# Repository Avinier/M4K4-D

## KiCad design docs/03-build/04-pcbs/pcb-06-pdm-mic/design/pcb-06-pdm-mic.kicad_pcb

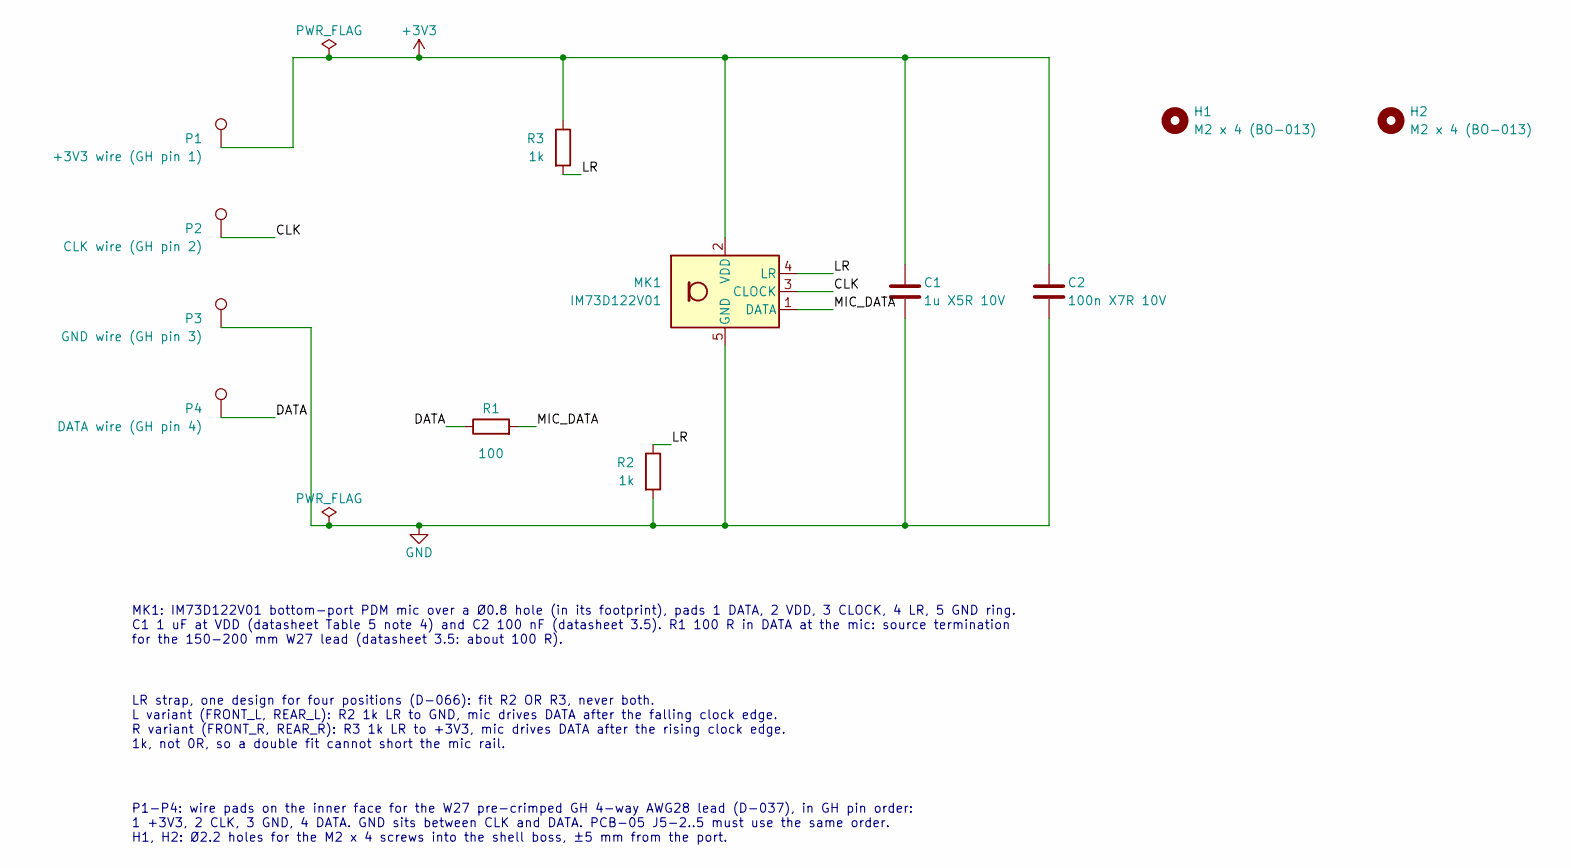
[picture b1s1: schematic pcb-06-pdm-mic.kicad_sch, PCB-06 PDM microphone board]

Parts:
C1: 1u X5R 10V; C_0402_1005Metric
C2: 100n X7R 10V; C_0402_1005Metric
H1, H2: M2 x 4 (BO-013); MountingHole_2.2mm_M2
MK1: IM73D122V01; IM73D122V01_PG-LLGA-5-3; MPN IM73D122V01XTMA1
P1: +3V3 wire (GH pin 1); WirePad_0.9x2.0mm
P2: CLK wire (GH pin 2); WirePad_0.9x2.0mm
P3: GND wire (GH pin 3); WirePad_0.9x2.0mm
P4: DATA wire (GH pin 4); WirePad_0.9x2.0mm
R1: 100; R_0402_1005Metric
R2, R3: 1k; R_0402_1005Metric

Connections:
+3V3: C1.1, C2.1, MK1.2 (VDD), P1.1 (1_1), R3.1
/CLK: MK1.3 (CLOCK), P2.1 (1_1)
/DATA: P4.1 (1_1), R1.1
/LR: MK1.4 (LR), R2.1, R3.2
/MIC_DATA: MK1.1 (DATA), R1.2
GND: C1.2, C2.2, MK1.5 (GND), P3.1 (1_1), R2.2

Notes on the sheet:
MK1: IM73D122V01 bottom-port PDM mic over a Ø0.8 hole (in its footprint), pads 1 DATA, 2 VDD, 3 CLOCK, 4 LR, 5 GND ring. C1 1 uF at VDD (datasheet Table 5 note 4) and C2 100 nF (datasheet 3.5). R1 100 R in DATA at the mic: source termination for the 150-200 mm W27 lead (datasheet 3.5: about 100 R).
LR strap, one design for four positions (D-066): fit R2 OR R3, never both. L variant (FRONT_L, REAR_L): R2 1k LR to GND, mic drives DATA after the falling clock edge. R variant (FRONT_R, REAR_R): R3 1k LR to +3V3, mic drives DATA after the rising clock edge. 1k, not 0R, so a double fit cannot short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
P1-P4: wire pads on the inner face for the W27 pre-crimped GH 4-way AWG28 lead (D-037), in GH pin order: 1 +3V3, 2 CLK, 3 GND, 4 DATA. GND sits between CLK and DATA. PCB-05 J5-2..5 must use the same order. H1, H2: Ø2.2 holes for the M2 x 4 screws into the shell boss, ±5 mm from the port.

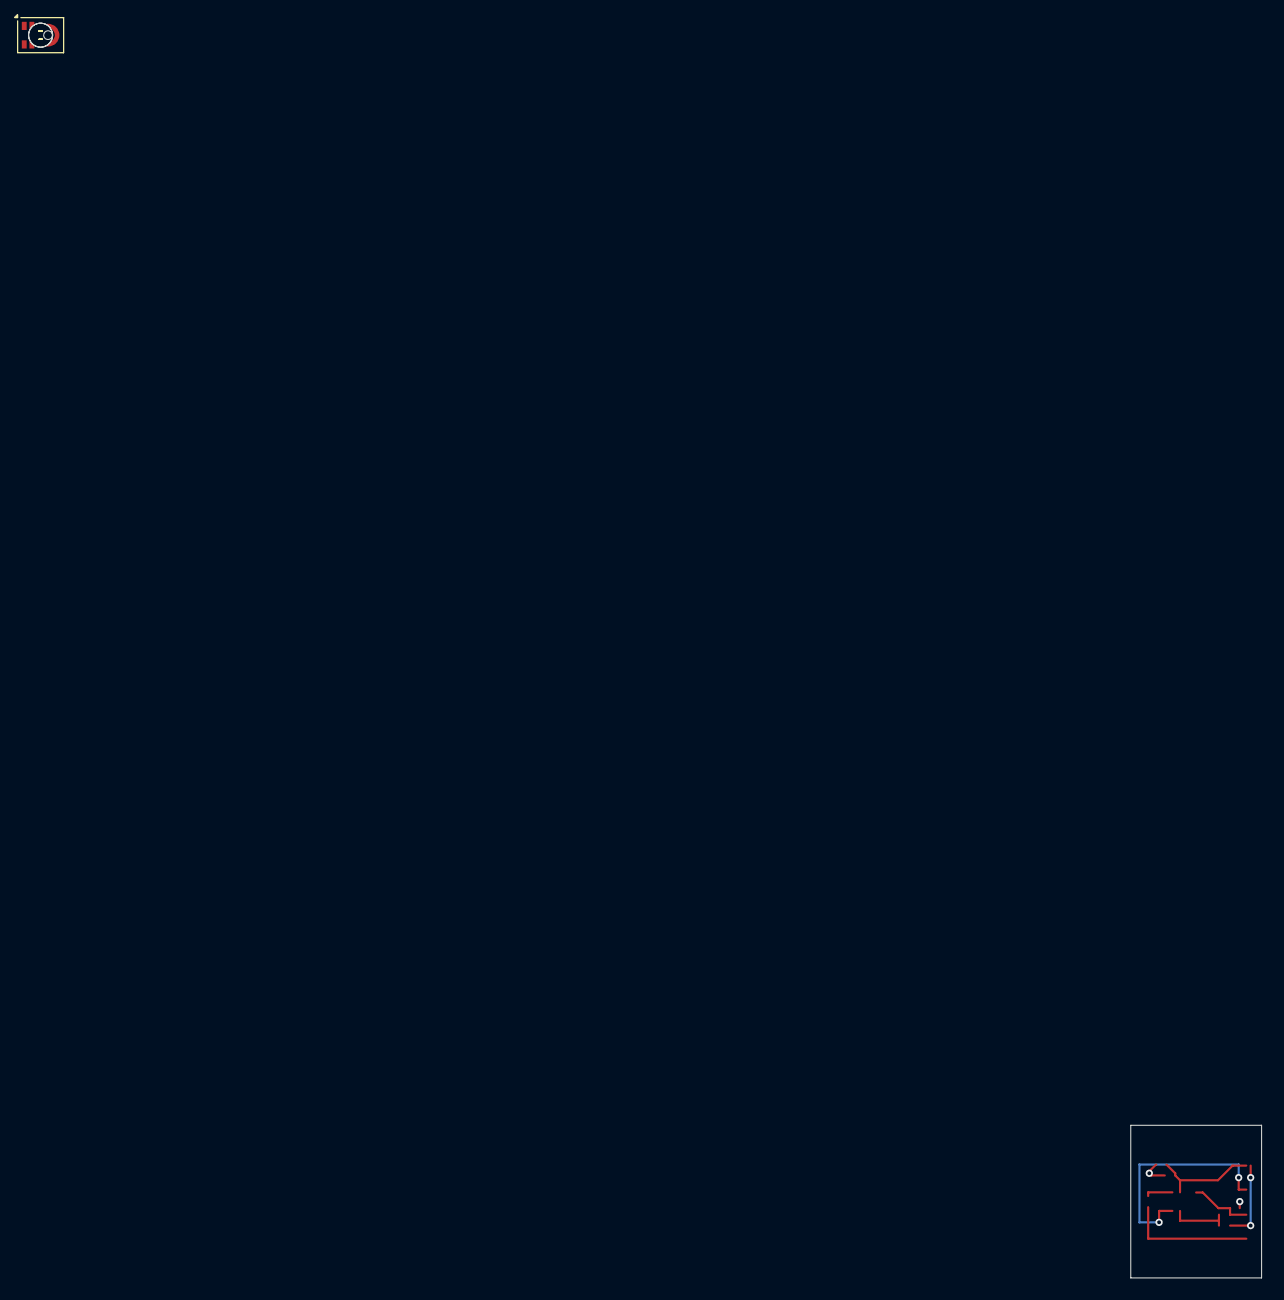
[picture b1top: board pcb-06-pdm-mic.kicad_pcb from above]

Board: 2 copper layers, 12.0 x 14.0 mm, 12 parts (0 on the bottom side), 6 nets.

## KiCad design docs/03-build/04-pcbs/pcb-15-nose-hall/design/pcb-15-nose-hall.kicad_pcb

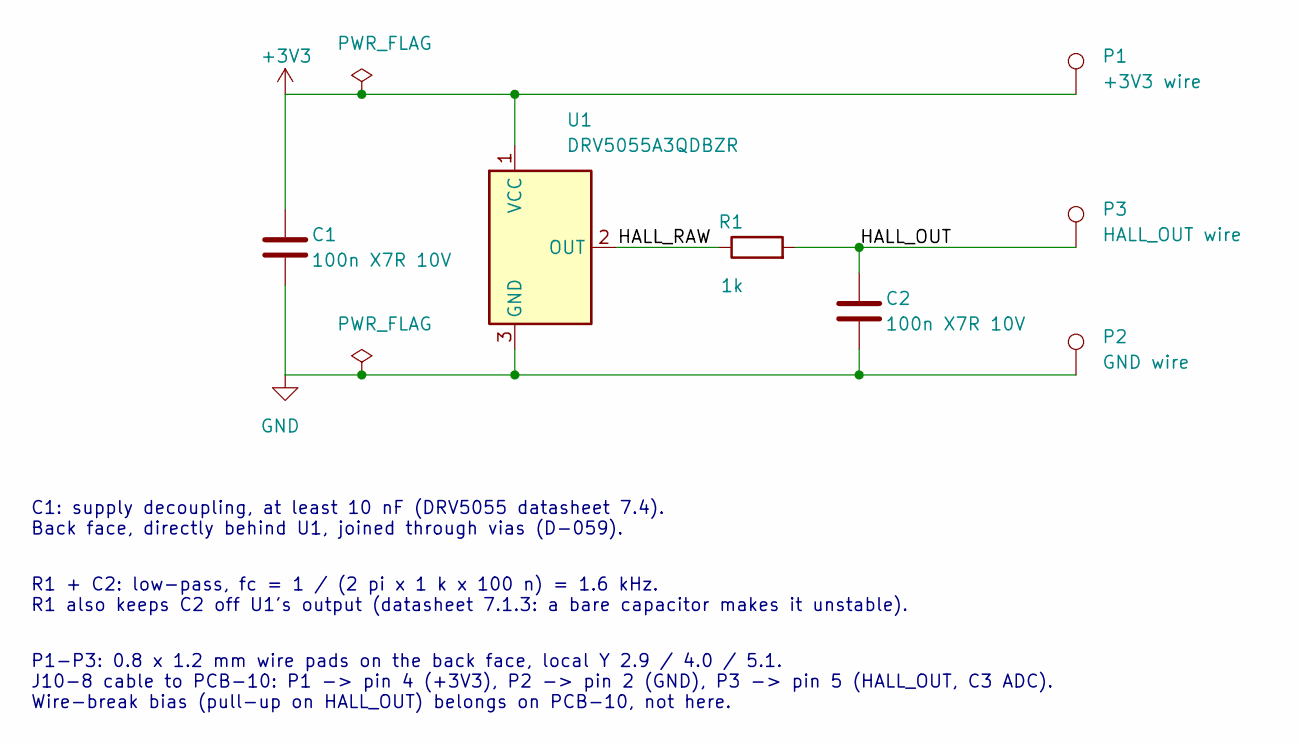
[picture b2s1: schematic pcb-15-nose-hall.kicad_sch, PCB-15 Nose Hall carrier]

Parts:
C1, C2: 100n X7R 10V; C_0402_1005Metric
P1: +3V3 wire; WirePad_0.8x1.2mm
P2: GND wire; WirePad_0.8x1.2mm
P3: HALL_OUT wire; WirePad_0.8x1.2mm
R1: 1k; R_0402_1005Metric
U1: DRV5055A3QDBZR; SOT-23_NoseNotch; MPN DRV5055A3QDBZR

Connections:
+3V3: C1.1, P1.1 (1_1), U1.1 (VCC)
/HALL_OUT: C2.1, P3.1 (1_1), R1.2
/HALL_RAW: R1.1, U1.2 (OUT)
GND: C1.2, C2.2, P2.1 (1_1), U1.3 (GND)

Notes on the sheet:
C1: supply decoupling, at least 10 nF (DRV5055 datasheet 7.4). Back face, directly behind U1, joined through vias (D-059).
R1 + C2: low-pass, fc = 1 / (2 pi x 1 k x 100 n) = 1.6 kHz. R1 also keeps C2 off U1's output (datasheet 7.1.3: a bare capacitor makes it unstable).
P1-P3: 0.8 x 1.2 mm wire pads on the back face, local Y 2.9 / 4.0 / 5.1. J10-8 cable to PCB-10: P1 -> pin 4 (+3V3), P2 -> pin 2 (GND), P3 -> pin 5 (HALL_OUT, C3 ADC). Wire-break bias (pull-up on HALL_OUT) belongs on PCB-10, not here.

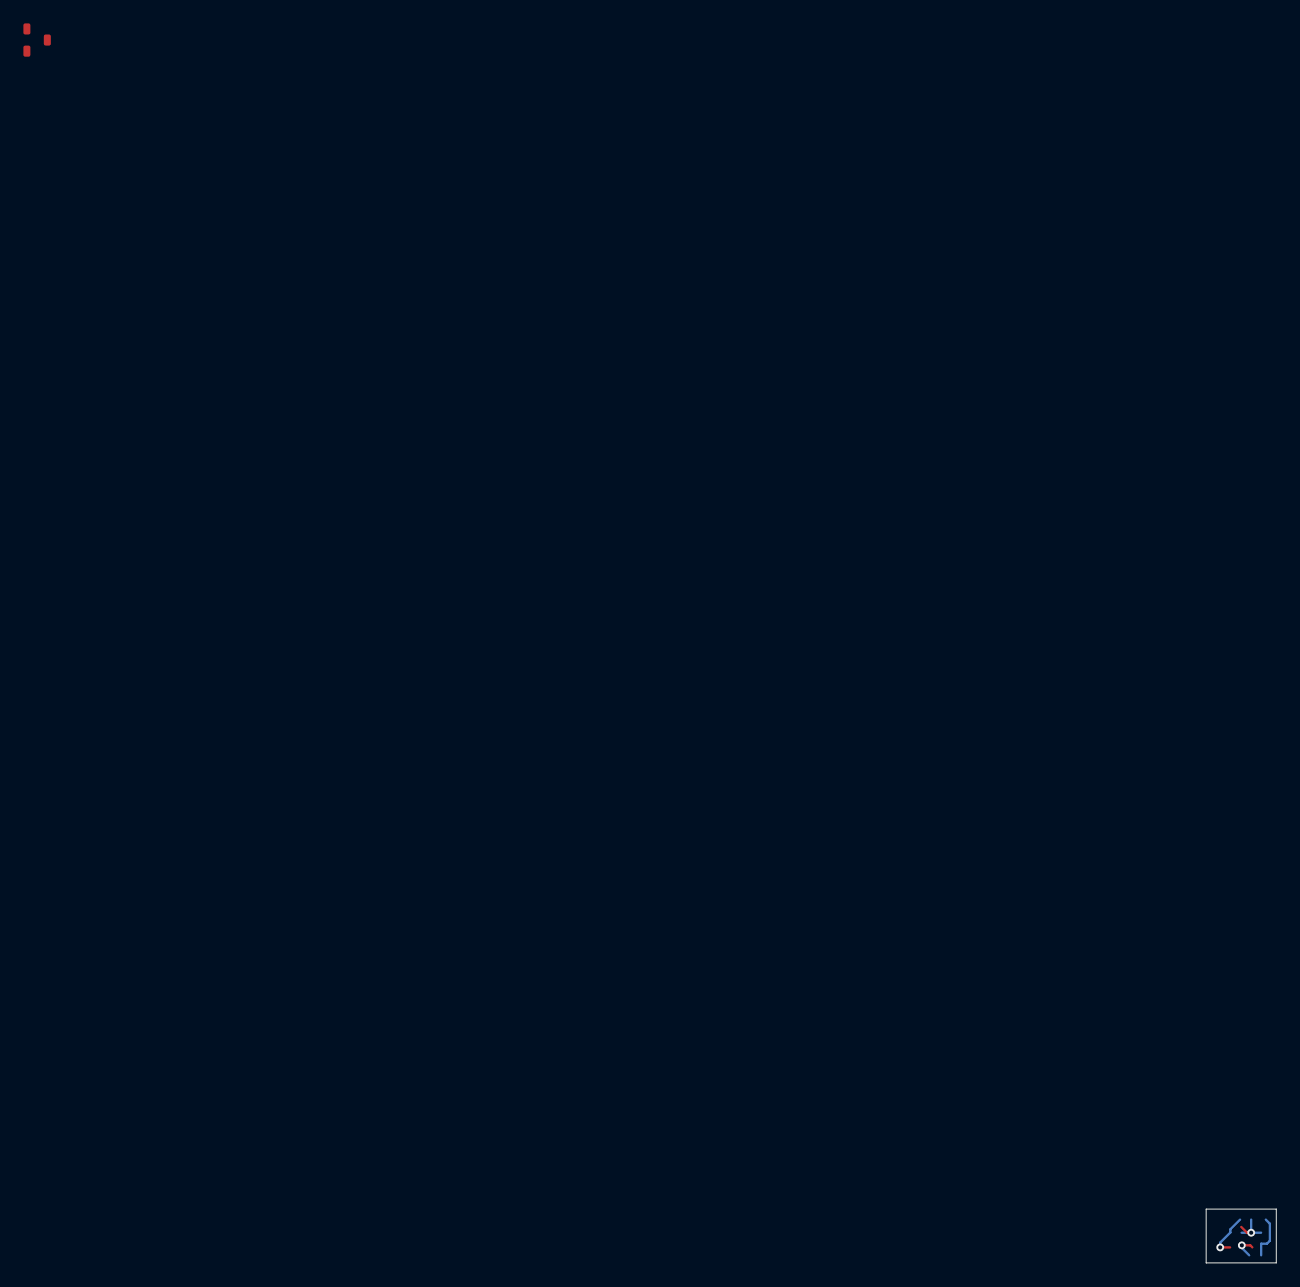
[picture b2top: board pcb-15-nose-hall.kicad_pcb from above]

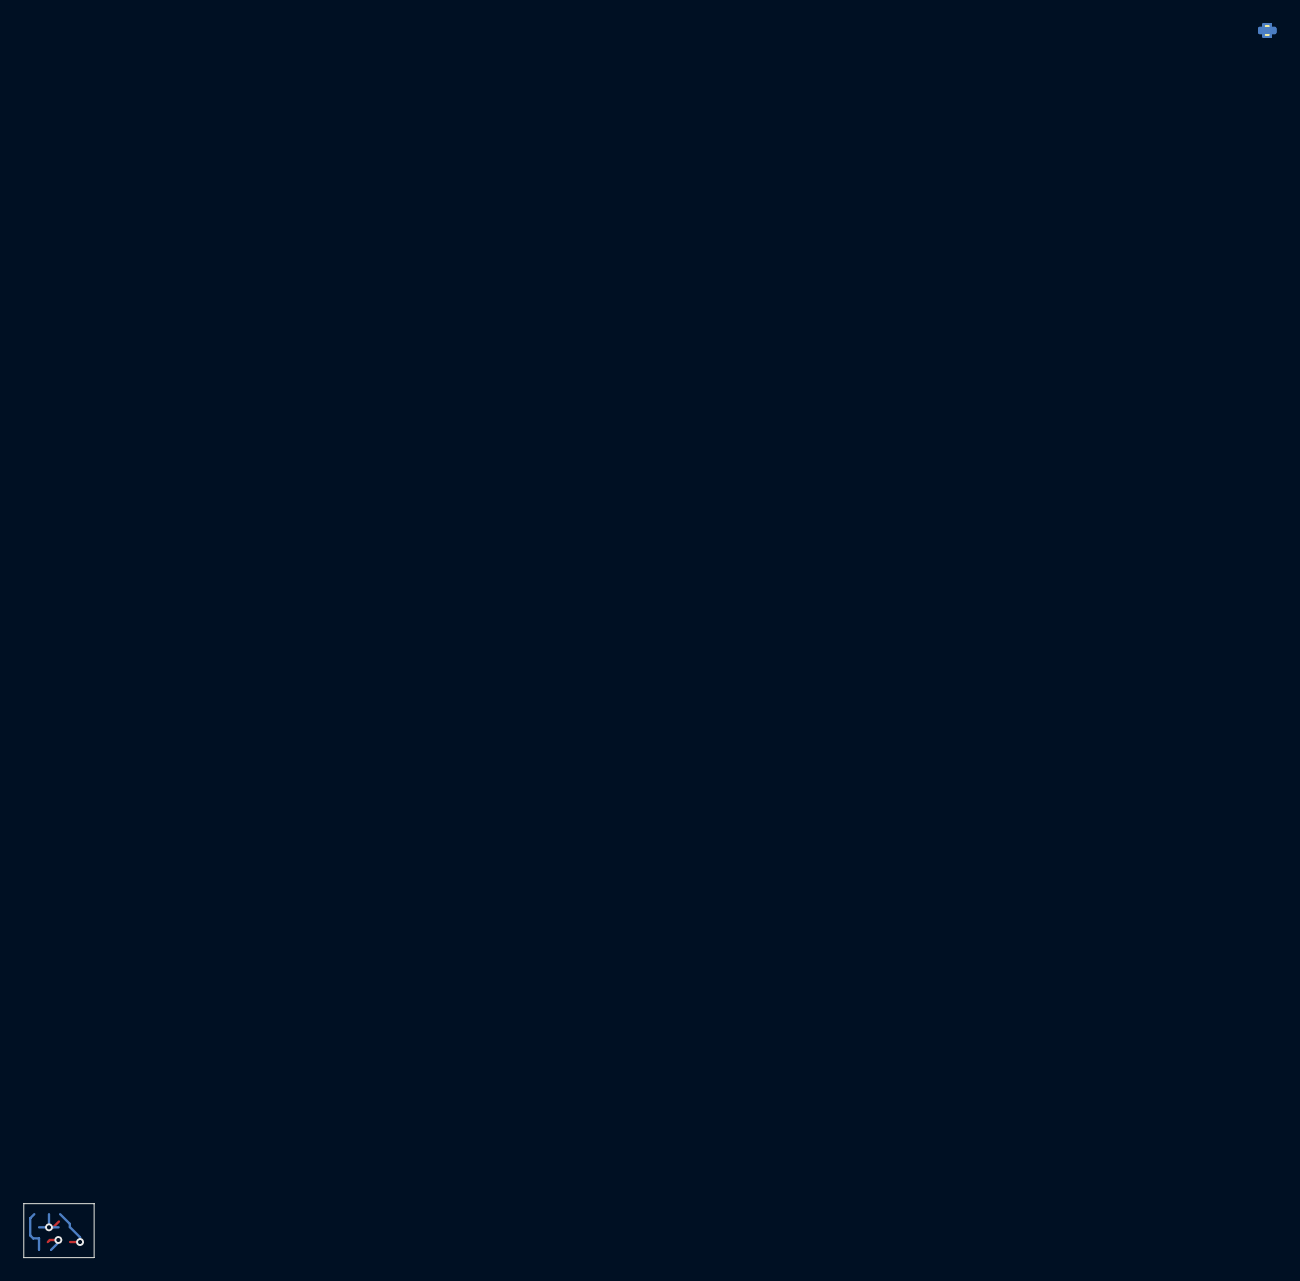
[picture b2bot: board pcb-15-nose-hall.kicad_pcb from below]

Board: 2 copper layers, 6.0 x 4.6 mm, 7 parts (6 on the bottom side), 4 nets.

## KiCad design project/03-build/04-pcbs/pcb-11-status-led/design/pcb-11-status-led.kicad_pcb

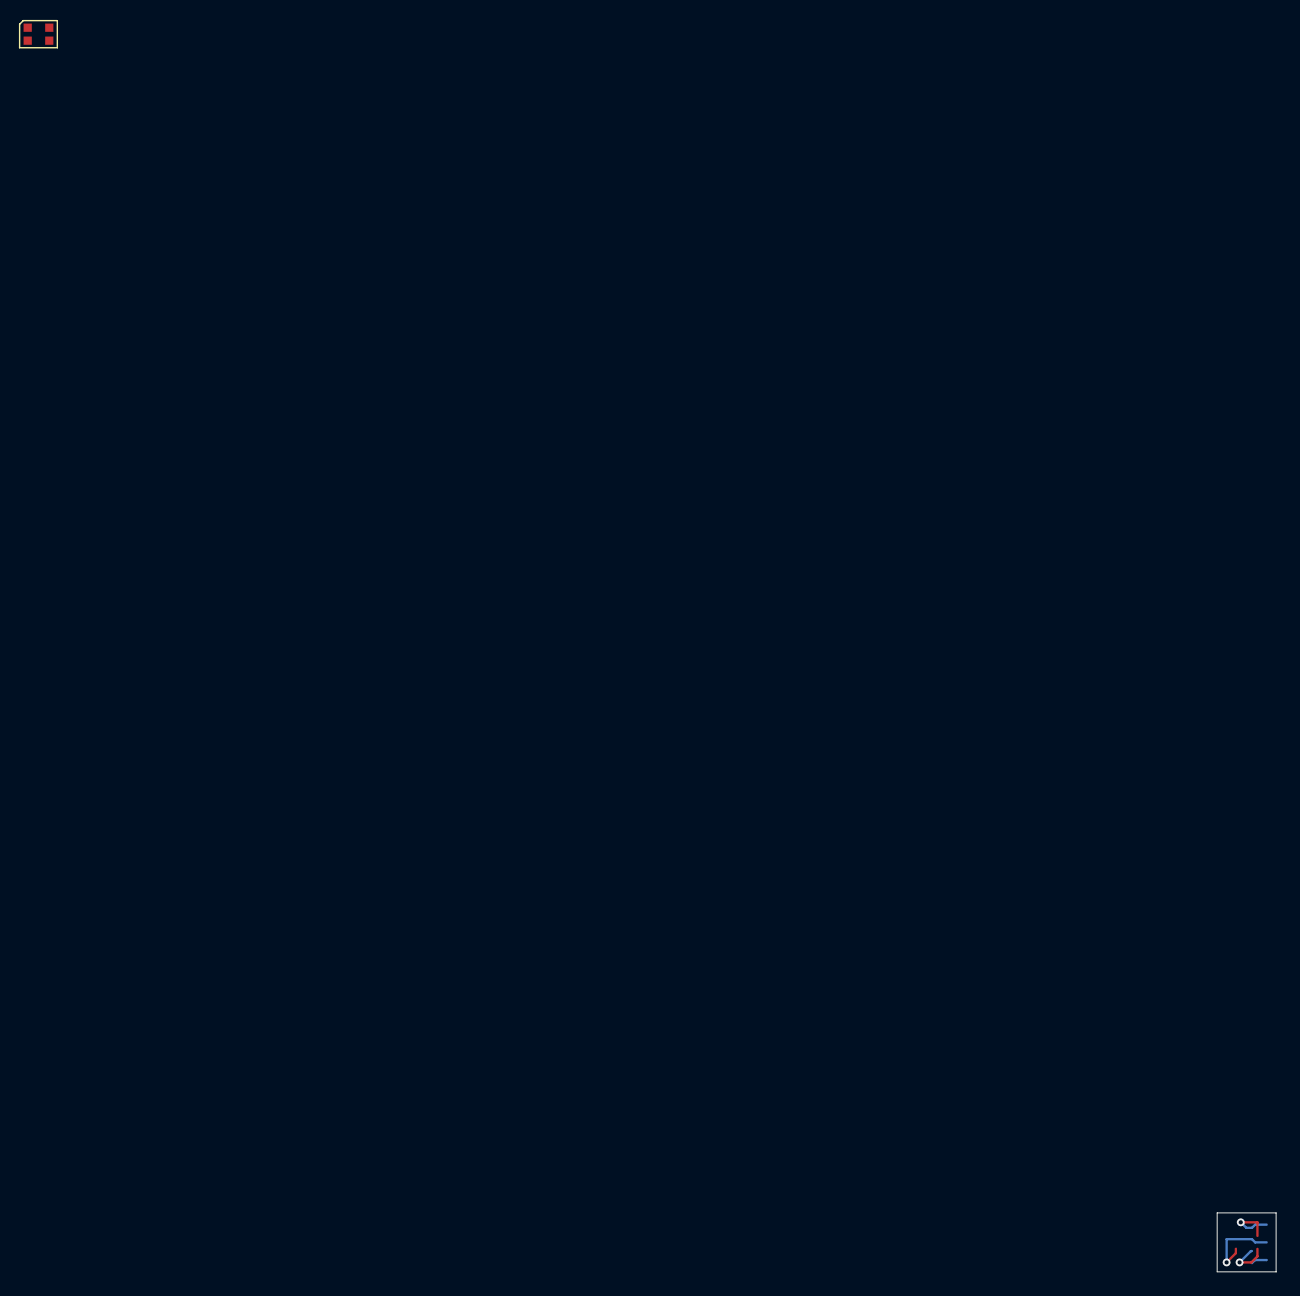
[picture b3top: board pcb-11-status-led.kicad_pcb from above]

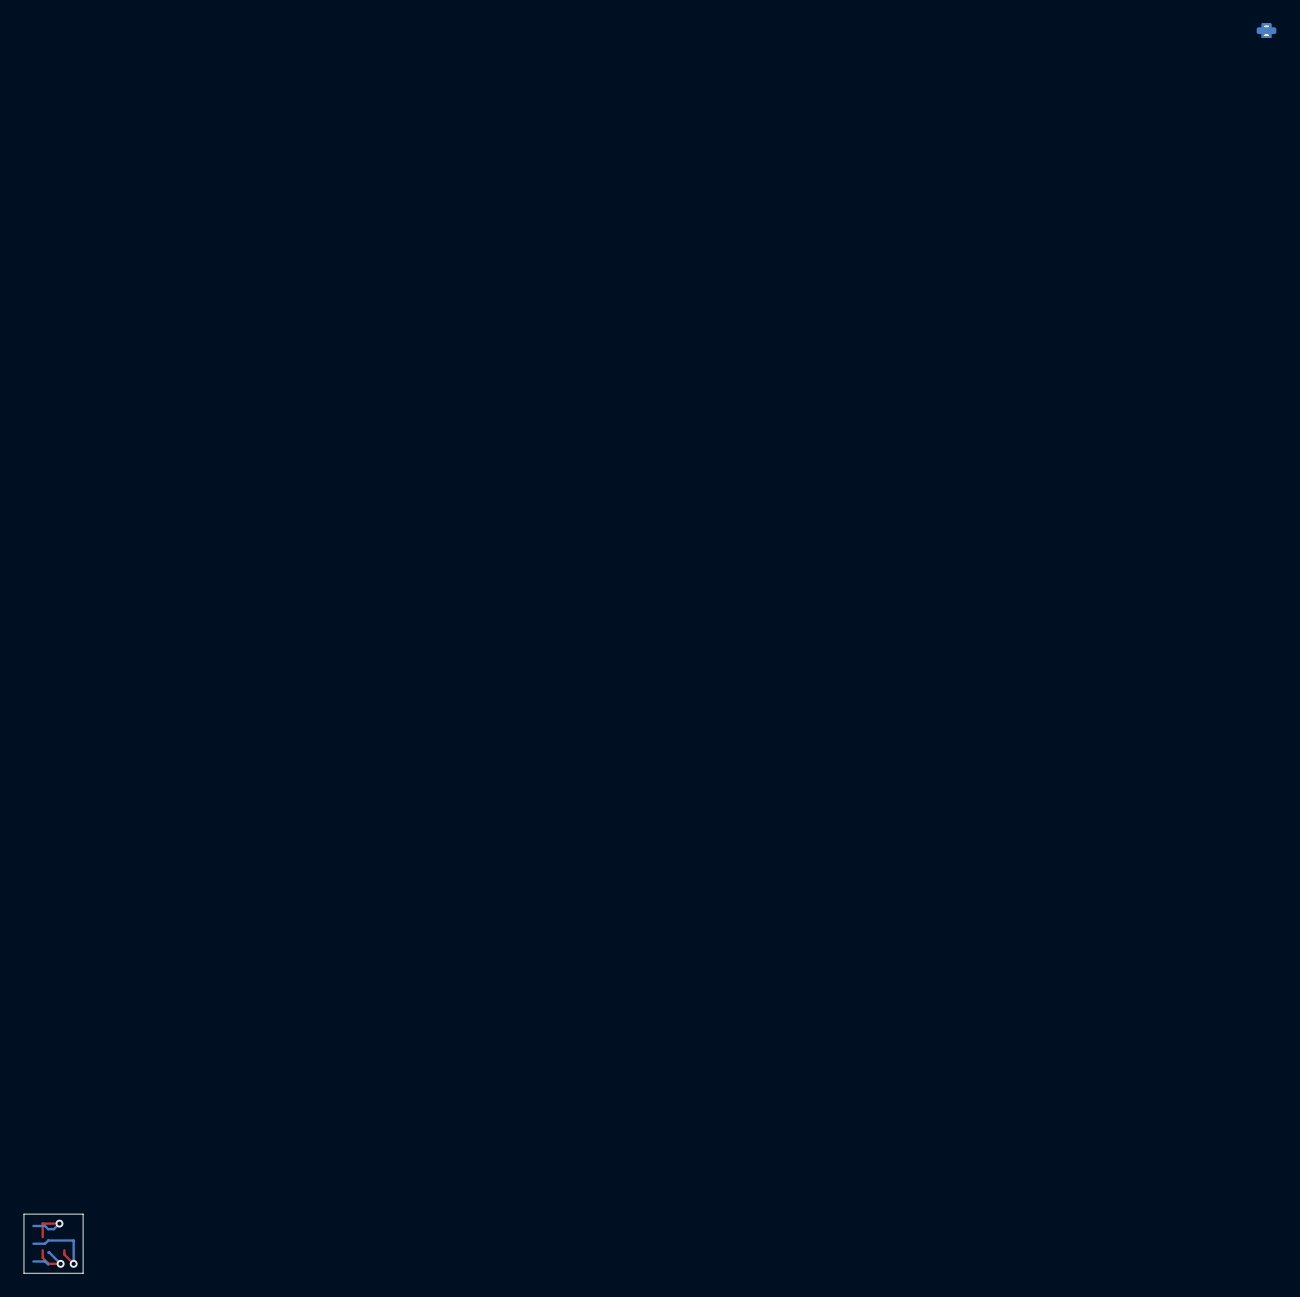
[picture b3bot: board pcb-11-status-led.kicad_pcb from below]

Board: 2 copper layers, 5.0 x 5.0 mm, 6 parts (5 on the bottom side), 4 nets.

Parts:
C1: 100n X7R 10V; C_0402_1005Metric
LED1: WS2812B-2020-V6; LED_WS2812B-2020-V6
P1: +3V3 wire; WirePad_0.8x1.2mm
P2: GND wire; WirePad_0.8x1.2mm
P3: DIN wire; WirePad_0.8x1.2mm
R1: 330; R_0402_1005Metric

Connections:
+3V3: C1.1, LED1.4 (VDD), P1.1 (1_1)
/DIN: P3.1 (1_1), R1.1
/LED_DIN: LED1.3 (DIN), R1.2
GND: C1.2, LED1.2 (VSS), P2.1 (1_1)
